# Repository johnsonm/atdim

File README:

This design for an attiny-based PWM dimmer circuit is licensed under
the CERN OHL as provided in the file cern_ohl_v_1_2.txt

This project requires that you set the open-project library references
to point to a checkout of git@github.com:open-project/kicadlibrary.git
The attiny part included is a variant on the version in the atmel
library with two pins moved for cosmetic purposes.

Options:

P1 may be 0.1" pitch header or screw terminal
Place P2 (ICSP) only if ICSP function desired
Three 4mm mounting holes provided

PHOTOR1 may be a 2-pin 0.1" header to a remote photoresistor
PHOTOR1 and R1 may be omitted if light sensing is not desired

FR1 may be a fusible resistor of an appropriate rating and value
for the load if the circuit is not otherwise protected, or a
jumper if it is sufficiently protected otherwise.

RV1 may be a 0.2" pitch potentiometer, a 0.1" pitch potentiometer,
a 0.1" pitch trim potentiometer, or a 3-conductor 0.1" or 0.2"
pitch connector (header or molex) to a remote potentiometer.
If you are using a 0.1" pitch part, solder the smaller pads first
as the middle pad's through-hole is sized to accomodate the larger
legs on typical 0.2" pitch potentiometers.

R3 is an optional pull-up resistor to ensure that the MOSFET
switches off cleanly at low duty cycle as described in.
https://gasstationwithoutpumps.wordpress.com/2014/07/28/pwm-controller/

D1 is a freewheel transient suppressing diode required only for
inductive loads such as motor control.

ATTINY85-T is any ATTINY*5 through-hole part that can hold your
desired program.

For low-profile applications:
Install ATTINY*5 directly soldered, not in a socket
U1 (7805) installed with bent leads over R2 and R3
Q1 (MOSFET) installed with bent leads over ATTINY*5
Use remote or low-profile potentiometer for RV1

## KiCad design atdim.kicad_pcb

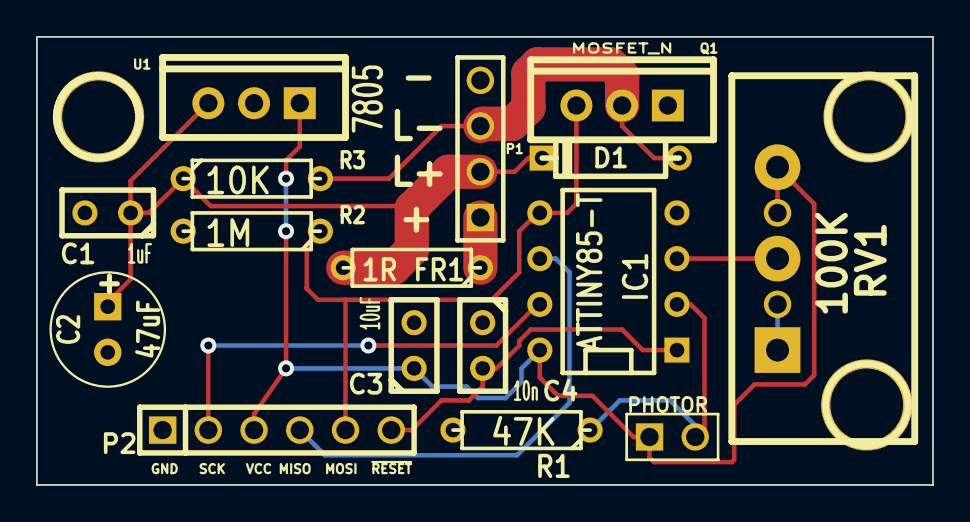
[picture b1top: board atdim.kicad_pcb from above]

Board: 2 copper layers, 49.8 x 24.9 mm, 20 parts (0 on the bottom side), 11 nets.

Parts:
1PIN, 1PIN#2, 1PIN#3, 1PIN#4: P***; 1pin
C1: 1uF; C1
C2: 47uF; C1V7
C3: 10uF; C1
C4: 10n; C1
D1: DIODE; D3
FR1: 1R; R3
IC1: ATTINY85-T; DIP-8__300
P1: CONN_4; PIN_ARRAY_4x1
P2: ICSP; PIN_ARRAY-6X1
PHOTOR1: PHOTOR; PIN_ARRAY_2X1
Q1: MOSFET_N; TO220_VERT
R1: 47K; R3
R2: 1M; R3
R3: 10K; R3
RV1: 100K; POTA_Fav
U1: 7805; TO220_VERT

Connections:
+12V: FR1.1, P1.1
/+12VS: C1.1, C2.1, D1.2, FR1.2, P1.2, R3.1, U1.VI
/ADC2: IC1.3, RV1.2
/ADC3: IC1.2, PHOTOR1.2, R1.1
/DRAIN: D1.1, P1.3, Q1.D, R3.2
/MISO: IC1.6, P2.4
/MOSI: IC1.5, P2.5, Q1.G, R2.1
/SCK: IC1.7, P2.2
/VCC: C3.1, IC1.8, P2.3, PHOTOR1.1, RV1.3, U1.VO
/~RESET: C4.2, IC1.1, P2.6
GND: C1.2, C2.2, C3.2, C4.1, IC1.4, P1.4, P2.1, Q1.S, R1.2, R2.2, RV1.1, U1.GND

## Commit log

2014-11-14 Initial version of attiny-based LED PWM dimmer circuit
2014-11-15 switch to 47K sense resistor for better match for 5549 response
2014-11-27 added pull-up resistor, changed some component values
    Added pull-up resistor based on writeup at
    https://gasstationwithoutpumps.wordpress.com/2014/07/28/pwm-controller/
    Modified suggested capacitor values based on additional perusal of
    data sheets for various versions of components.
    Modified suggested R1 value based on experiments with my existing LDRs
2014-11-27 add annotations on silkscreen for parts and connections
2014-12-08 mark RESET pin with overbar
2014-12-08 rearrange board: separate power from logic, no need for reverse mounting or folding capacitor leads
2014-12-08 add a fusible resistor
2014-12-08 add a freewheel diode just in case I ever want to use this for motor control
2014-12-08 increase trace width for higher power
2014-12-10 freewheel diode in schematic
2015-01-15 reflow ground plane around freewheel diode
